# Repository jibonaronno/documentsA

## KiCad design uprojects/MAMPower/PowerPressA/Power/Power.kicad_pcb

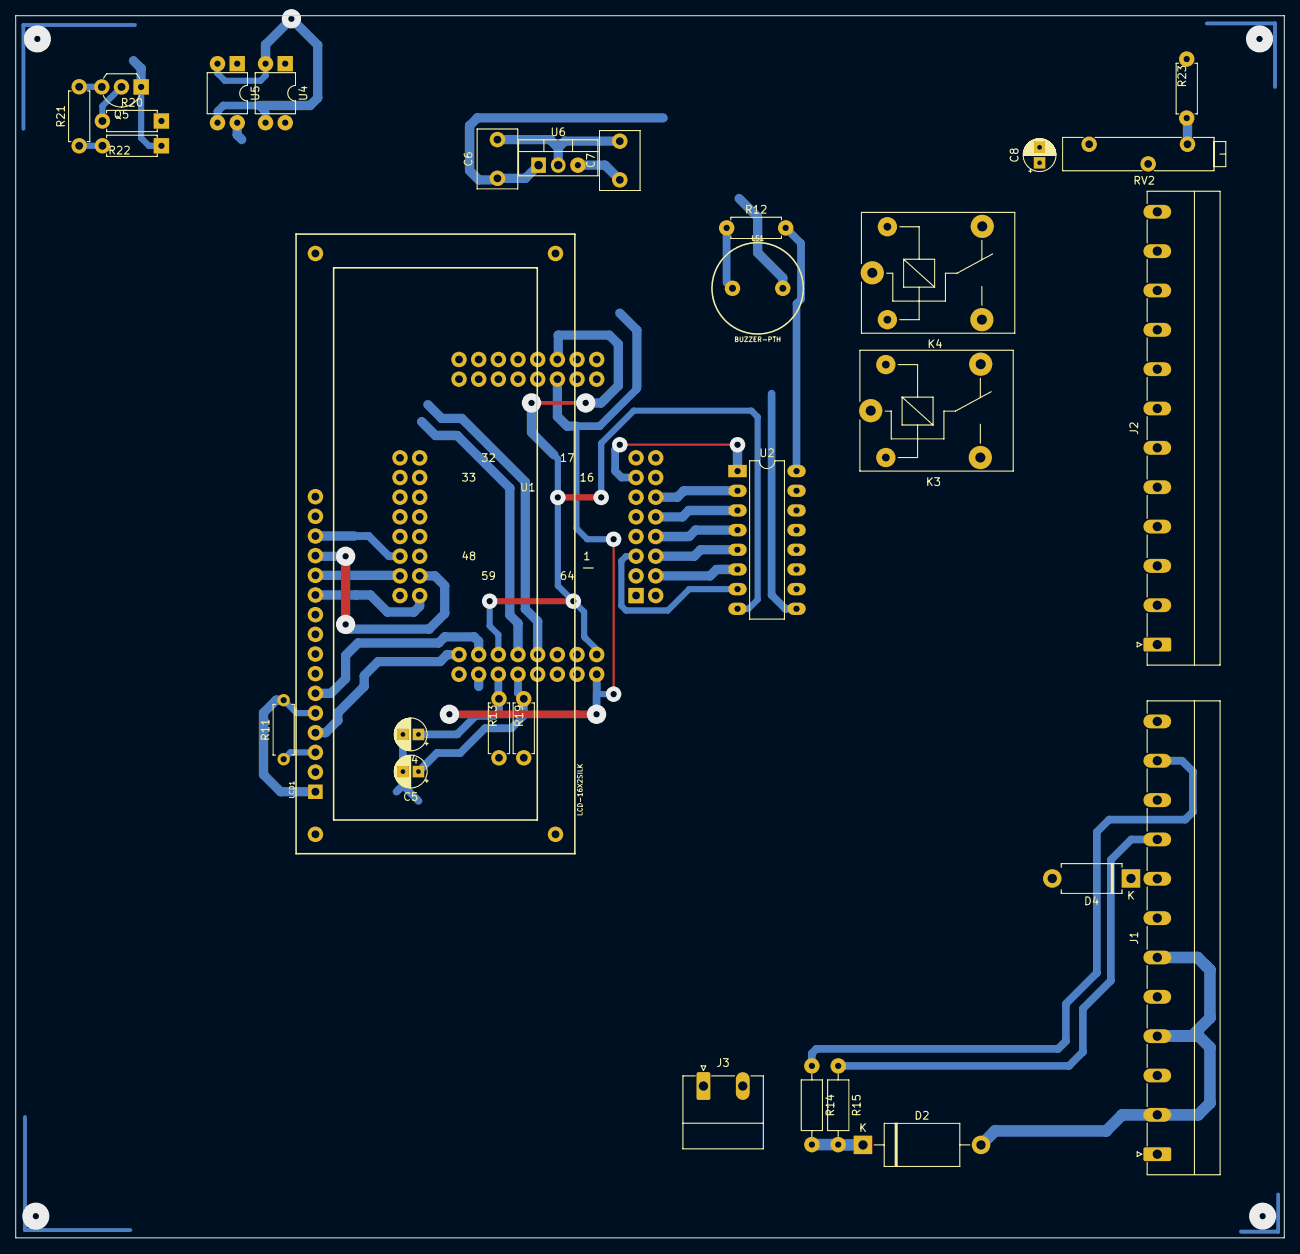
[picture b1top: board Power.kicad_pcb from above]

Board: 2 copper layers, 163.8 x 157.8 mm, 31 parts (0 on the bottom side), 39 nets.

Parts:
C4, C5, C8: CP; CP_Radial_D4.0mm_P2.00mm
C6, C7: C_Small; C_Disc_D7.5mm_W5.0mm_P5.00mm
D2: D_Small; D_DO-27_P15.24mm_Horizontal
D4: D_Small; D_DO-15_P10.16mm_Horizontal
J1, J2: Conn_01x12; PhoenixContact_MC_1,5_12-G-5.08_1x12_P5.08mm_Horizontal
J3: Conn_01x02; PhoenixContact_MC_1,5_2-G-5.08_1x02_P5.08mm_Horizontal
K3, K4: SANYOU_SRD_Form_C; Relay_SPDT_SANYOU_SRD_Series_Form_C
LCD1: LCD-16X2SILK; LCD-16X2
LS1: BUZZER-PTH; BUZZER-12MM
Q5: PN2222A; TO-92L_Inline_Wide
R11, R13, R19, R20, R22: 3K3; R_Axial_DIN0207_L6.3mm_D2.5mm_P7.62mm_Horizontal
R12: 100E; R_Axial_DIN0207_L6.3mm_D2.5mm_P7.62mm_Horizontal
R14, R15: 22K; R_Axial_DIN0207_L6.3mm_D2.5mm_P10.16mm_Horizontal
R21: 1k; R_Axial_DIN0207_L6.3mm_D2.5mm_P7.62mm_Horizontal
R23: 75K; R_Axial_DIN0207_L6.3mm_D2.5mm_P7.62mm_Horizontal
RV2: 10K; Potentiometer_Bourns_3005_Horizontal
U1: ATmega128A-AU; TQFP64.Break
U2: ULN2003A; DIP-16_W7.62mm_LongPads
U4, U5: PC817; DIP-4_W7.62mm
U6: LM7805_TO220; TO-220-3_Vertical

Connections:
10: U1.10, U2.3
12: U1.12, U2.2
13: U1.13, U2.1
48V: D2.2, J1.2, J1.4, J1.6, R23.1
+12V: C6.1, D4.2, K3.5, K4.5, LS1.+, U2.9, U6.1
+48V: D2.1, R14.2, R15.2
ADC5: C5.1, R19.1, U1.56
ADC7: C4.1, R13.1, U1.54
BKLED: R20.2, U1.40
D4: LCD1.11, U1.47
D5: LCD1.12, U1.46
D6: LCD1.13, U1.45
D7: LCD1.14, U1.44
DOOR: J1.10, U4.1
DOORT: U1.57, U4.4
E: LCD1.6, U1.51
GND: C4.2, C5.2, C6.2, C7.2, C8.2, J3.2, LCD1.1, LCD1.5, Q5.1, R11.2, R22.2, RV2.1, U1.22, U1.53, U1.63, U2.8, U4.2, U4.3, U5.2, U5.3, U6.2
LED-: LCD1.16, R21.1, R22.1
unnamed: D4.1, J1.8
unnamed: J1.1, J3.1
unnamed: J1.9, R15.1
unnamed: J1.11, R14.1
unnamed: LCD1.3, R11.1
unnamed: LS1.-, R12.1
unnamed: Q5.2, R20.1
unnamed: Q5.3, R21.2
unnamed: R12.2, U2.16
unnamed: R23.2, RV2.3
unnamed: U1.4, U2.6
unnamed: U1.5, U2.7
unnamed: U1.6, U2.5
unnamed: U1.8, U2.4
REL3: K3.2, U2.12
REL4: K4.2, U2.13
RS: LCD1.4, U1.49
VBat: C8.1, RV2.2, U1.61
VCC: C7.1, LCD1.2, LCD1.15, U1.21, U1.52, U1.64, U6.3
WATER: J1.12, U5.1
WATERT: U1.55, U5.4

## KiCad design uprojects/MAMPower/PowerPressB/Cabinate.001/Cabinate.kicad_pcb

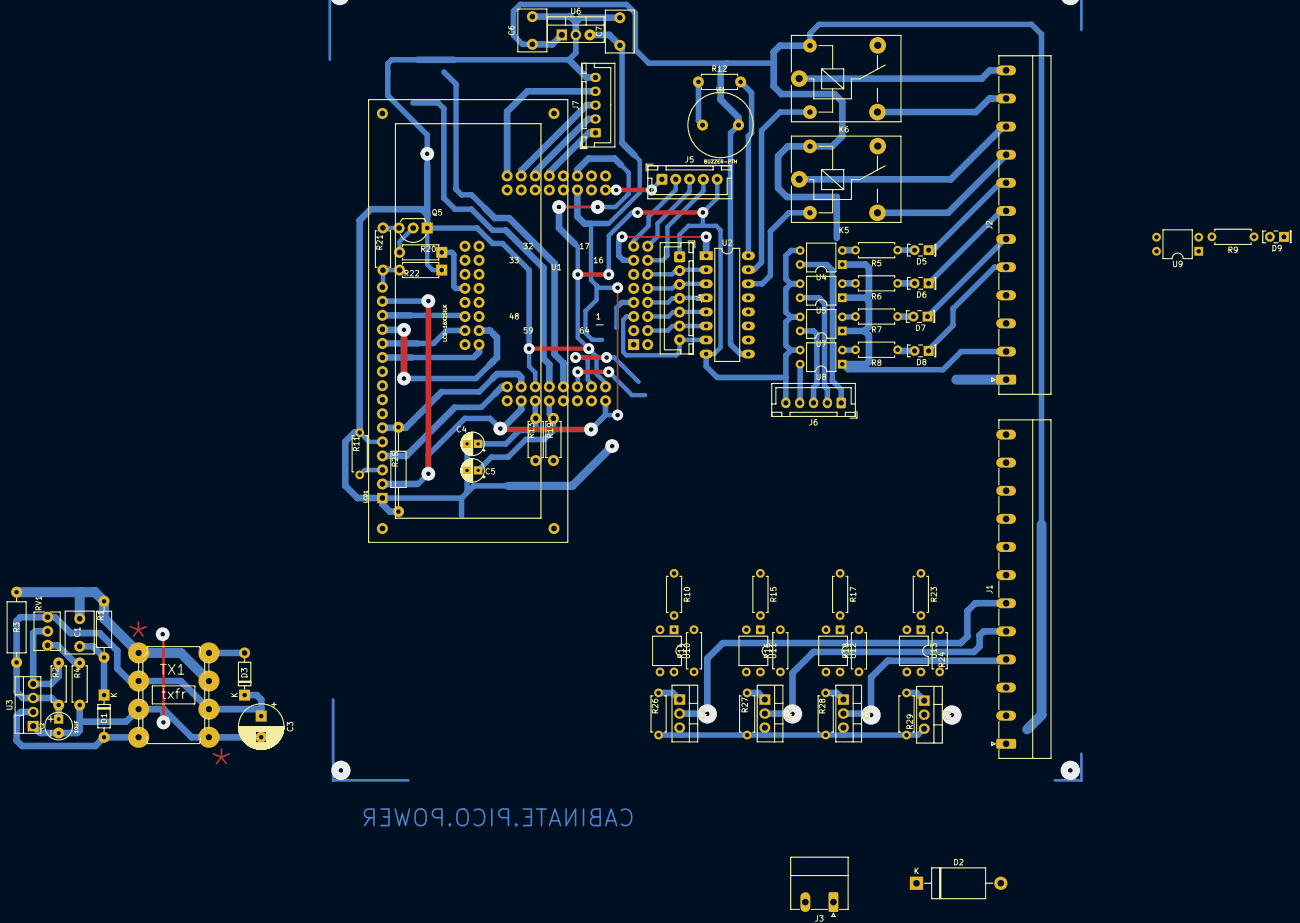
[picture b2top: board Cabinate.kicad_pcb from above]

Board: 2 copper layers, 75 parts (0 on the bottom side), 87 nets.

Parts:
C1: 103/1KV; C_Disc_D7.5mm_W5.0mm_P5.00mm
C2: 10UF; CPOL-RADIAL-2.5MM-5MM
C3: 100uF; CP_Radial_D8.0mm_P3.80mm
C4, C5: CP; CP_Radial_D4.0mm_P2.00mm
C6, C7: C_Small; C_Disc_D7.5mm_W5.0mm_P5.00mm
D1, D3: FR107; D_DO-35_SOD27_P7.62mm_Horizontal
D2: D_Small; D_DO-27_P15.24mm_Horizontal
D5, D6, D7, D8, D9: LED_Small; LED_Rectangular_W5.0mm_H2.0mm
J1, J2: Conn_01x12; PhoenixContact_MC_1,5_12-G-5.08_1x12_P5.08mm_Horizontal
J3: Conn_01x02; PhoenixContact_MC_1,5_2-G-5.08_1x02_P5.08mm_Horizontal
J4: Conn_01x07; JST_XH_B7B-XH-A_1x07_P2.50mm_Vertical
J5, J6, J7: Conn_01x05; JST_XH_B5B-XH-A_1x05_P2.50mm_Vertical
K5, K6: SANYOU_SRD_Form_C; Relay_SPDT_SANYOU_SRD_Series_Form_C
LCD1: LCD-16X2SILK; LCD-16X2
LS1: BUZZER-PTH; BUZZER-12MM
Q1, Q2, Q3, Q4: TIP122; TO-220-3_Vertical
Q5: PN2222A; TO-92L_Inline_Wide
R1: 33K1W; R_Axial_DIN0207_L6.3mm_D2.5mm_P10.16mm_Horizontal
R2: 1M; R_Axial_DIN0207_L6.3mm_D2.5mm_P7.62mm_Horizontal
R3: 47K1W; R_Axial_DIN0309_L9.0mm_D3.2mm_P12.70mm_Horizontal
R4: 2K2; R_Axial_DIN0207_L6.3mm_D2.5mm_P7.62mm_Horizontal
R5, R6, R7, R8, R9, R11, R13, R19, R20, R22: 3K3; R_Axial_DIN0207_L6.3mm_D2.5mm_P7.62mm_Horizontal
R10, R14, R15, R16, R17, R18, R23, R24: 270E; R_Axial_DIN0207_L6.3mm_D2.5mm_P7.62mm_Horizontal
R12: 100E; R_Axial_DIN0207_L6.3mm_D2.5mm_P7.62mm_Horizontal
R21: 1k; R_Axial_DIN0207_L6.3mm_D2.5mm_P7.62mm_Horizontal
R25: 3K3; R_Axial_DIN0207_L6.3mm_D2.5mm_P15.24mm_Horizontal
R26, R27, R28, R29: 100K; R_Axial_DIN0207_L6.3mm_D2.5mm_P7.62mm_Horizontal
RV1: 10K; Potentiometer_Bourns_3266Y_Vertical
TX1: txfr; -INDUCTOR_MEDIUM
U1: ATmega128A-AU; TQFP64.Break
U2: ULN2003A; DIP-16_W7.62mm_LongPads
U3: KA5L0265RTU; TO-220-4_Vertical
U4, U5, U7, U8, U9, U10, U11, U12, U13: PC817; DIP-4_W7.62mm
U6: LM7805_TO220; TO-220-3_Vertical

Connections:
4: J4.6, U1.4, U2.6
5: J4.7, U1.5, U2.7
6: J4.5, U1.6, U2.5
8: J4.4, U1.8, U2.4
10: J4.3, U1.10, U2.3
12: J4.2, U1.12, U2.2
13: U1.13, U2.1
+12V: C2.1, C3.1, C6.1, D3.1, K5.5, K6.5, LS1.+, R2.1, R3.2, RV1.3, TX1.P$2, TX1.P$6, U2.9, U3.3, U6.1
+24V: J2.2, U4.1, U5.1, U7.1, U8.1, U9.1
+48V: C1.1, D2.1, R1.2, R3.1, TX1.P$1, TX1.P$7
A1: D5.1, J2.8
A2: D7.1, J2.6
ADC5: C5.1, R19.1, U1.56
ADC7: C4.1, R13.1, U1.54
B1: D6.1, J2.7
B2: D8.1, J2.5
BKLED: R20.2, U1.40
D4: LCD1.11, U1.47
D5: LCD1.12, U1.46
D6: LCD1.13, U1.45
D7: LCD1.14, U1.44
E: LCD1.6, R25.1, U1.51
ENC1: J5.4, U1.14
ENC2: J5.2, U1.15
ENC3: J5.3, U1.16
ENC4: J5.1, U1.17
GND: C2.2, C3.2, C4.2, C5.2, C6.2, C7.2, J2.1, J3.2, J4.1, J5.5, J6.5, J7.5, LCD1.1, LCD1.5, Q1.3, Q2.3, Q3.3, Q4.3, Q5.1, R4.1, R11.2, R22.2, R25.2, R26.2, R27.2, R28.2, R29.2, TX1.P$3, TX1.P$5, U1.22, U1.53, U1.63, U2.8, U3.1, U4.3, U5.3, U6.2, U7.3, U8.3, U9.3, U10.2, U11.2, U12.2, U13.2
LED-: LCD1.16, R21.1, R22.1
unnamed: C1.2, D1.1, R1.1
unnamed: D1.2, TX1.P$4, U3.2
unnamed: D2.2, J1.2
unnamed: D3.2, TX1.P$8
unnamed: D5.2, R5.1
unnamed: D6.2, R6.1
unnamed: D7.2, R7.1
unnamed: D8.2, R8.1
unnamed: D9.2, R9.1
unnamed: J1.1, J3.1
unnamed: J2.9, K5.3
unnamed: J2.10, K5.1
unnamed: J2.11, K6.3
unnamed: J2.12, K6.1
unnamed: J6.1, U4.4
unnamed: J6.2, U5.4
unnamed: J6.3, U7.4
unnamed: J6.4, U8.4
unnamed: J7.1, U1.26
unnamed: J7.2, U1.28
unnamed: J7.3, U1.30
unnamed: J7.4, U1.32
unnamed: LCD1.3, R11.1
unnamed: LS1.-, R12.1
unnamed: Q1.1, R29.1, U13.3
unnamed: Q2.1, R27.1, U11.3
unnamed: Q3.1, R28.1, U12.3
unnamed: Q4.1, R26.1, U10.3
unnamed: Q5.2, R20.1
unnamed: Q5.3, R21.2
unnamed: R2.2, RV1.2, U3.4
unnamed: R4.2, RV1.1
unnamed: R5.2, U4.2
unnamed: R6.2, U5.2
unnamed: R7.2, U7.2
unnamed: R8.2, U8.2
unnamed: R9.2, U9.2
unnamed: R10.2, U10.1
unnamed: R12.2, U2.16
unnamed: R14.1, U10.4
unnamed: R15.2, U11.1
unnamed: R16.1, U11.4
unnamed: R17.2, U12.1
unnamed: R18.1, U12.4
unnamed: R23.2, U13.1
unnamed: R24.1, U13.4
Q4: R23.1, U1.61
Q5: R17.1, U1.59
Q6: R15.1, U1.60
Q7: R10.1, U1.58
REL5: K5.2, U2.14
REL6: K6.2, U2.15
RS: LCD1.4, U1.49
SOL1: J1.3, Q1.2
SOL2: J1.4, Q3.2
SOL3: J1.5, Q2.2
SOL4: J1.6, Q4.2
SW1: D9.1, J2.4
VCC: C7.1, LCD1.2, LCD1.15, R14.2, R16.2, R18.2, R24.2, U1.21, U1.52, U1.64, U6.3

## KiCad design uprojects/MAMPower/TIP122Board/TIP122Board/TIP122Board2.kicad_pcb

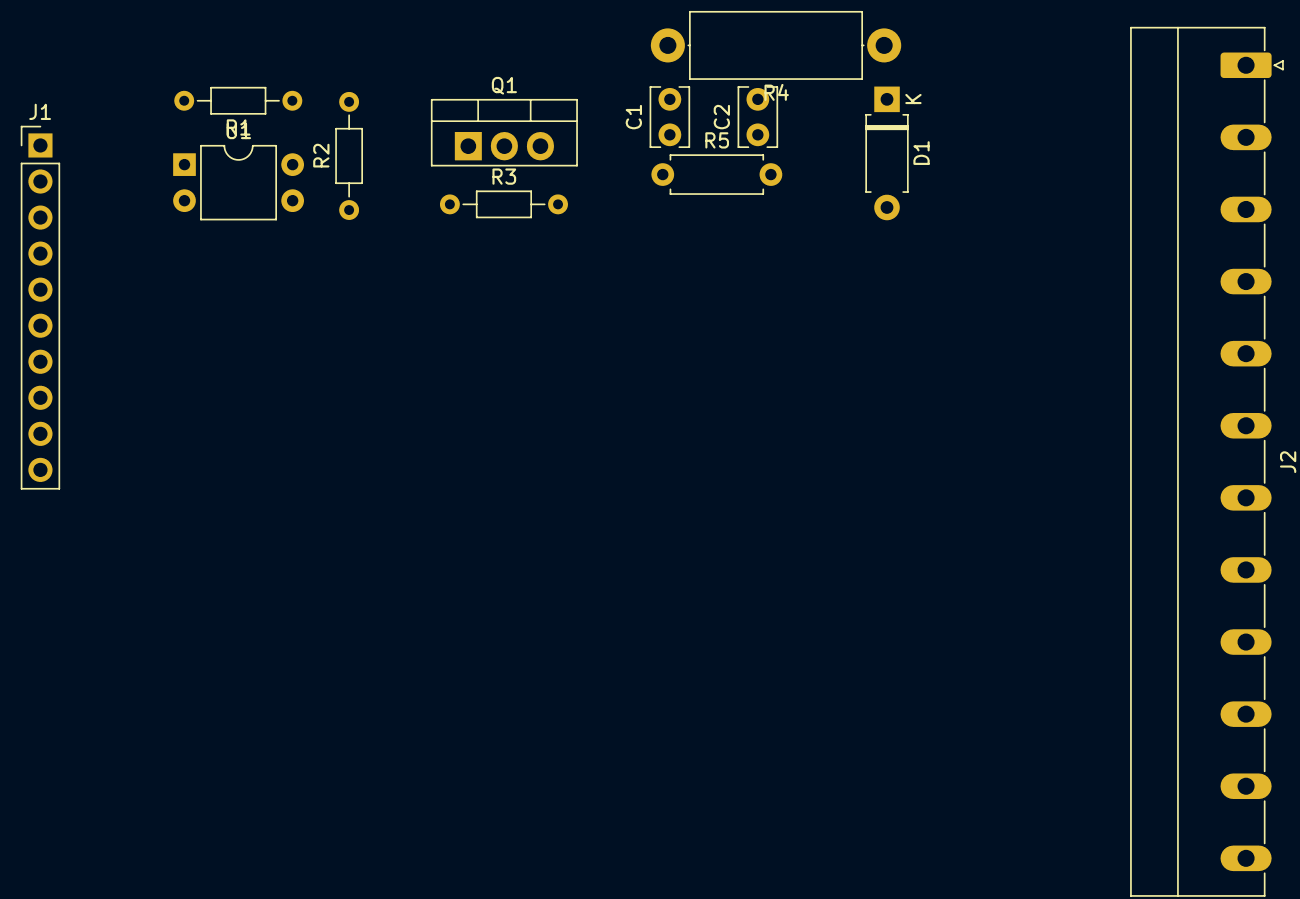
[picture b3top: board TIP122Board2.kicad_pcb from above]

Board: 2 copper layers, 12 parts (0 on the bottom side), 9 nets, no tracks yet.

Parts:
C1, C2: 0.1/400; C_Rect_L4.0mm_W2.5mm_P2.50mm
D1: D_Schottky; D_A-405_P7.62mm_Horizontal
J1: Conn_01x10; PinHeader_1x10_P2.54mm_Vertical
J2: Conn_01x12; PhoenixContact_MC_1,5_12-G-5.08_1x12_P5.08mm_Horizontal
Q1: TIP122; TO-220-3_Vertical
R1, R2: 270; R_Axial_DIN0204_L3.6mm_D1.6mm_P7.62mm_Horizontal
R3: 22K; R_Axial_DIN0204_L3.6mm_D1.6mm_P7.62mm_Horizontal
R4: 47E 5W; R_Axial_DIN0414_L11.9mm_D4.5mm_P15.24mm_Horizontal
R5: 22K 1W; R_Axial_DIN0207_L6.3mm_D2.5mm_P7.62mm_Horizontal
U1: PC817; DIP-4_W7.62mm

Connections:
24V: D1.1, J2.11
GND: J1.10, U1.2
GND2: J2.12, Q1.3, R3.2, R4.2
unnamed: C1.1, C2.1, D1.2, J2.1, Q1.2, R5.1
unnamed: C1.2, C2.2, R4.1, R5.2
unnamed: J1.1, R1.2
unnamed: Q1.1, R3.1, U1.3
unnamed: R1.1, U1.1
unnamed: R2.2, U1.4

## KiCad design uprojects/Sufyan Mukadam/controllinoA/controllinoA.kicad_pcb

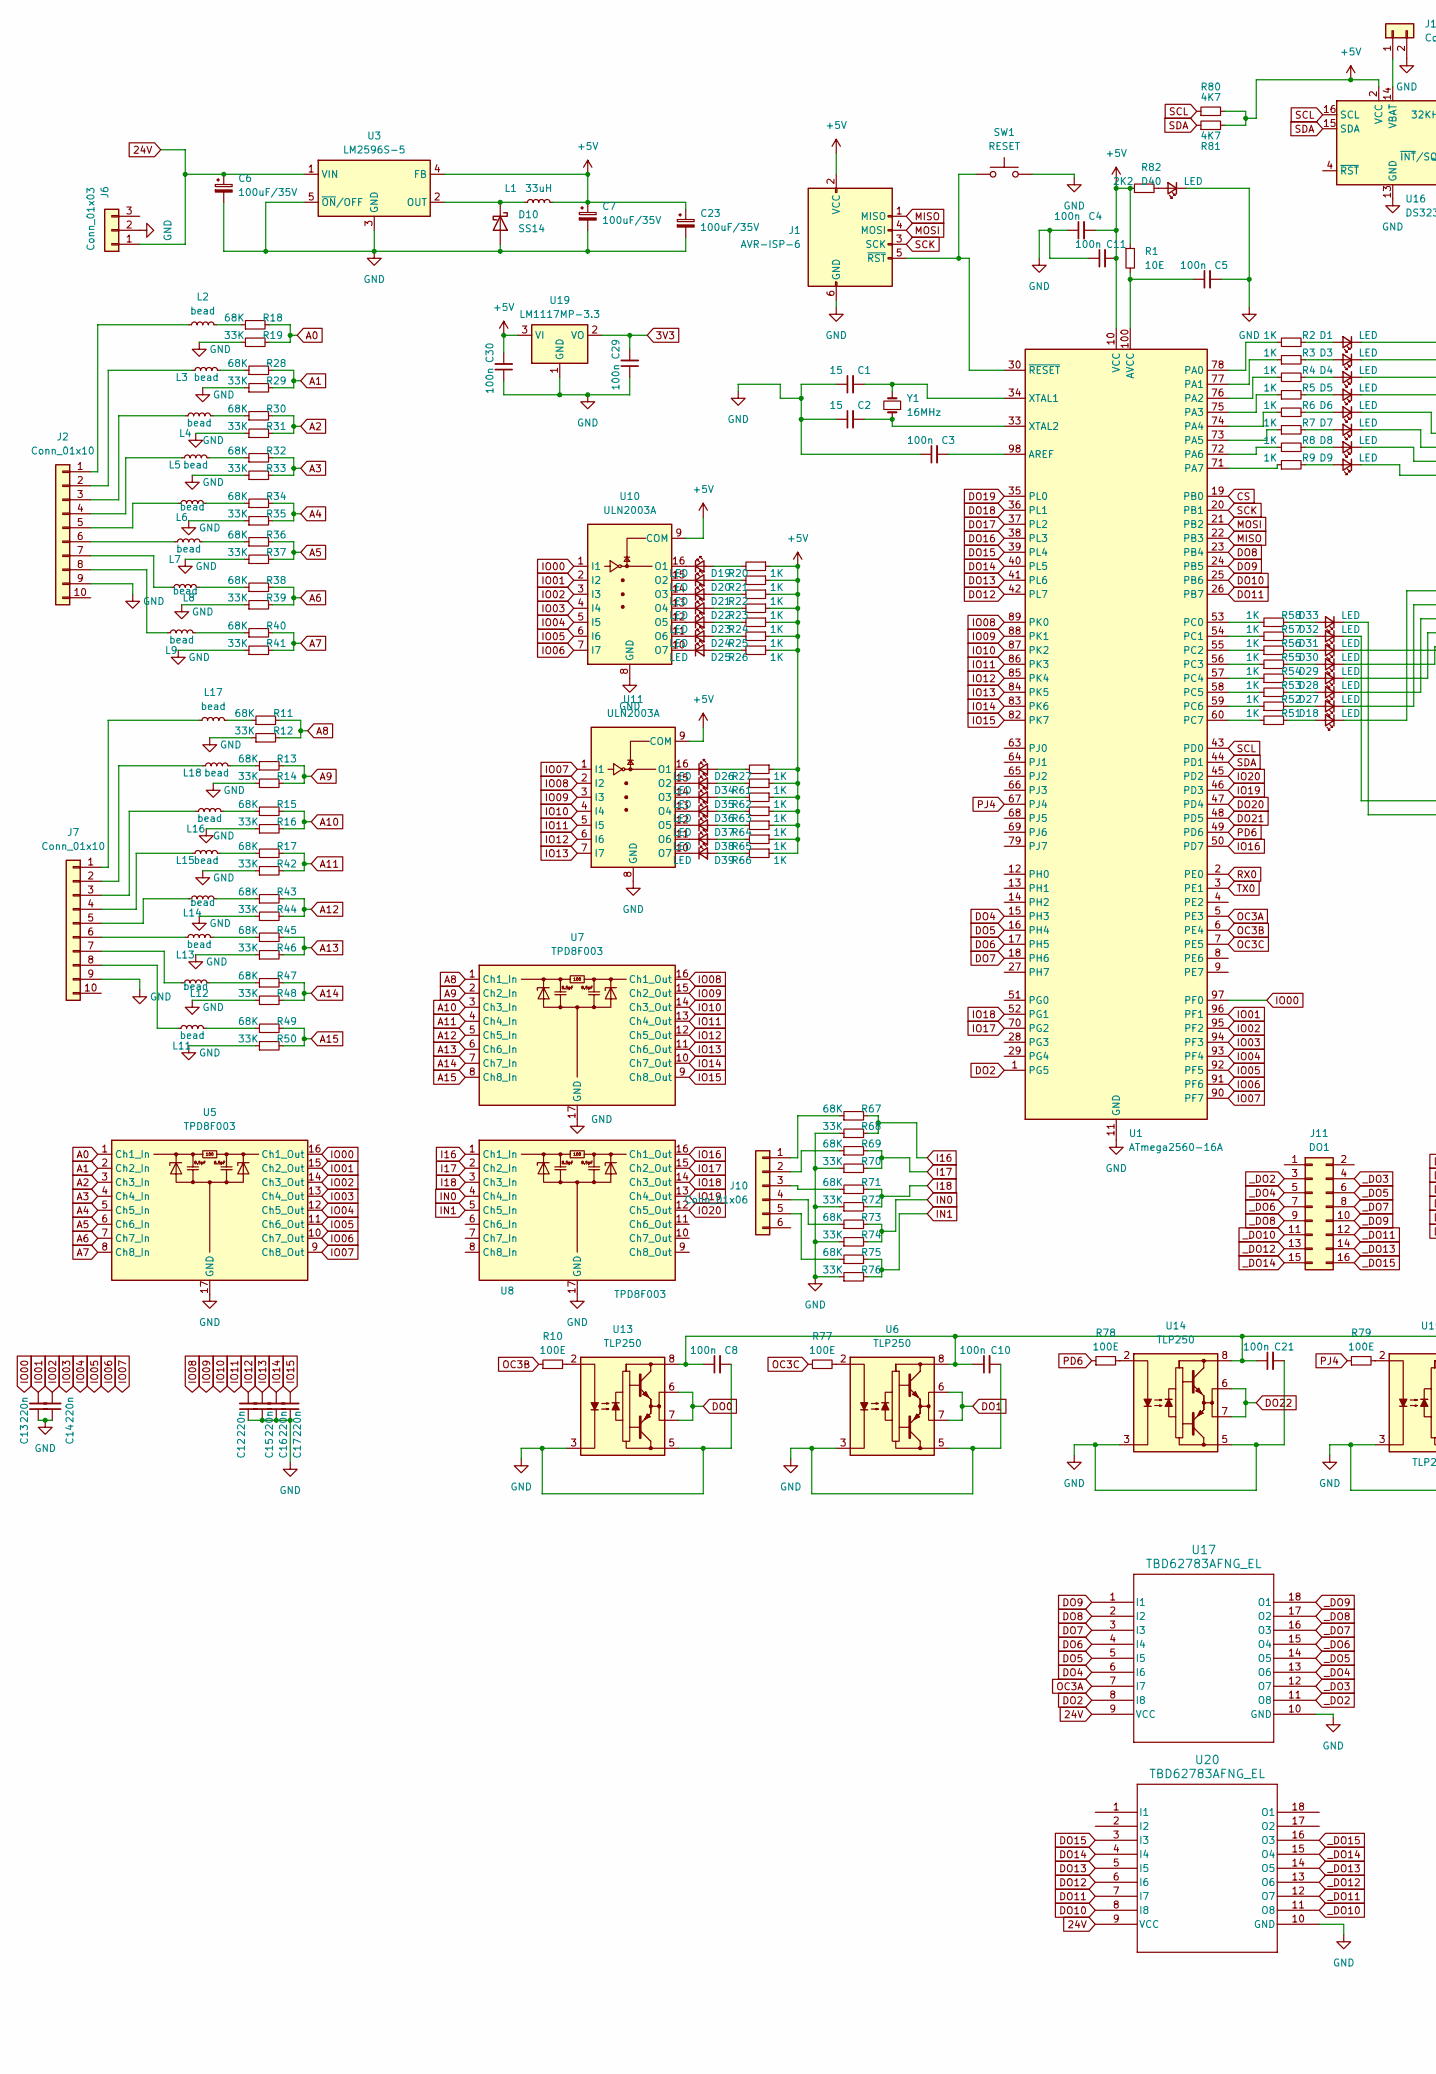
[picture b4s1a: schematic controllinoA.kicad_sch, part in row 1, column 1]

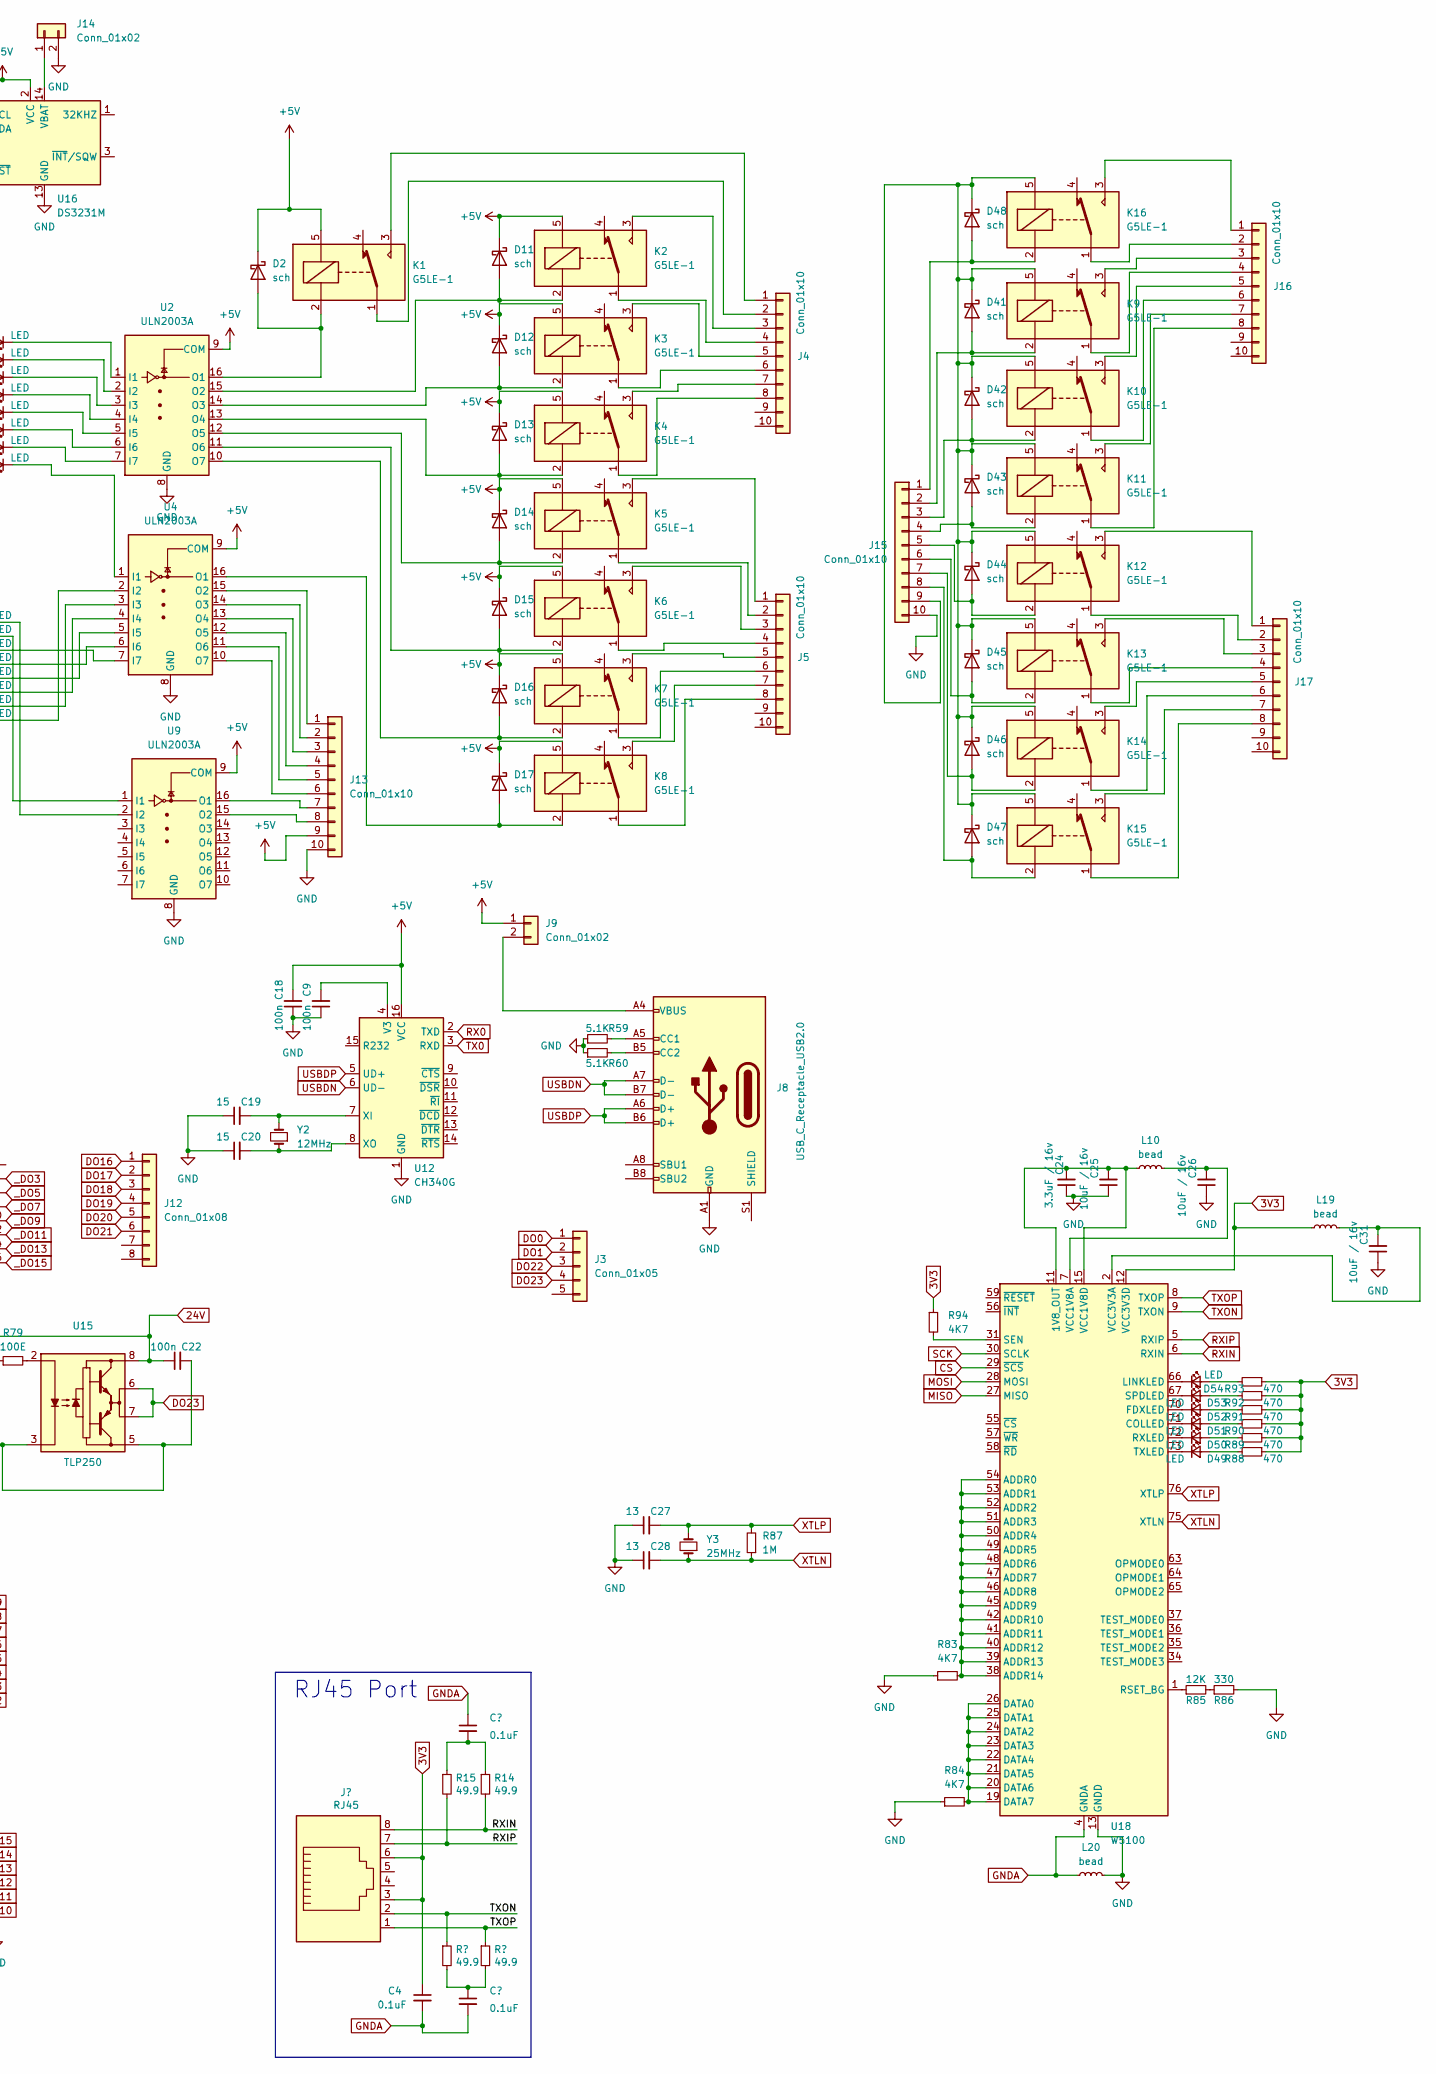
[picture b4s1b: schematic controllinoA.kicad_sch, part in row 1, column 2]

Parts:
C1, C2, C19, C20: 15; C_0805_2012Metric_Pad1.18x1.45mm_HandSolder
C3, C5, C8, C9, C10, C11, C18, C21, C22, C29, C30: 100n; C_0805_2012Metric_Pad1.18x1.45mm_HandSolder
C4, C33, C34: 0.1uF; C_0603_1608Metric
C6, C7, C23: 100uF/35V; CP_Elec_6.3x7.7
C12, C13, C14, C15, C16, C17: 220n; C_0603_1608Metric
C24: 3.3uF / 16v; C_0805_2012Metric_Pad1.18x1.45mm_HandSolder
C25, C26, C31: 10uF / 16v; C_0805_2012Metric_Pad1.18x1.45mm_HandSolder
C27, C28: 13; C_0805_2012Metric_Pad1.18x1.45mm_HandSolder
D1, D3, D4, D5, D6, D7, D8, D9, D18, D19, D20, D21, D22, D23, D24, D25, D26, D27, D28, D29, D30, D31, D32, D33, D34, D35, D36, D37, D38, D39, D40, D49, D50, D51, D52, D53, D54: LED; LED_0805_2012Metric_Pad1.15x1.40mm_HandSolder
D2, D11, D12, D13, D14, D15, D16, D17, D41, D42, D43, D44, D45, D46, D47, D48: sch; D_SOD-128
D10: SS14; D_SOD-128
J1: AVR-ISP-6; IDC-Header_2x03_P2.54mm_Vertical
J2, J7: Conn_01x10; PinHeader_1x10_P2.54mm_Vertical
J3: Conn_01x05; PinHeader_1x05_P2.54mm_Vertical
J4, J5, J16, J17: Conn_01x10; PhoenixContact_MCV_1,5_10-G-3.5_1x10_P3.50mm_Vertical
J6: Conn_01x03; PhoenixContact_MCV_1,5_3-G-5.08_1x03_P5.08mm_Vertical
J8: USB_C_Receptacle_USB2.0; USB_C_Receptacle_HCTL_HC-TYPE-C-16P-01A
J9: Conn_01x02; PinHeader_1x02_P2.54mm_Vertical
J10: Conn_01x06; PinHeader_1x06_P2.54mm_Vertical
J11: DO1; PinHeader_2x08_P2.54mm_Vertical
J12: Conn_01x08; PinHeader_1x08_P2.54mm_Vertical
J13, J15: Conn_01x10; JST_XH_B10B-XH-A_1x10_P2.50mm_Vertical
J14: Conn_01x02; JST_XH_B2B-XH-A_1x02_P2.50mm_Vertical
J18: RJ45; RJ45_Amphenol_54602-x08_Horizontal
K1, K2, K3, K4, K5, K6, K7, K8, K9, K10, K11, K12, K13, K14, K15, K16: G5LE-1; Relay_SPDT_Omron-G5LE-1
L1: 33uH; L_Bourns_SRR1210A
L2, L3, L4, L5, L6, L7, L8, L9, L10, L11, L12, L13, L14, L15, L16, L17, L18, L19, L20: bead; L_1206_3216Metric
R1: 10E; R_0805_2012Metric_Pad1.20x1.40mm_HandSolder
R2, R3, R4, R5, R6, R7, R8, R9, R20, R21, R22, R23, R24, R25, R26, R27, R51, R52, R53, R54, R55, R56, R57, R58, R61, R62, R63, R64, R65, R66: 1K; R_0805_2012Metric_Pad1.20x1.40mm_HandSolder
R10, R77, R78, R79: 100E; R_0805_2012Metric_Pad1.20x1.40mm_HandSolder
R11, R13, R17, R18, R28, R30, R32, R34, R36, R38, R40, R43, R45, R47, R49, R67, R69, R71, R73, R75: 68K; R_0805_2012Metric_Pad1.20x1.40mm_HandSolder
R12, R14, R16, R19, R29, R31, R33, R35, R37, R39, R41, R42, R44, R46, R48, R50, R68, R70, R72, R74, R76: 33K; R_0805_2012Metric_Pad1.20x1.40mm_HandSolder
R15, R96, R98: 49.9; R_0603_1608Metric
R59, R60: 5.1K; R_0805_2012Metric_Pad1.20x1.40mm_HandSolder
R80, R81, R83, R84, R94: 4K7; R_0805_2012Metric_Pad1.20x1.40mm_HandSolder
R82: 2K2; R_0805_2012Metric_Pad1.20x1.40mm_HandSolder
R85: 12K; R_0805_2012Metric_Pad1.20x1.40mm_HandSolder
R86: 330; R_0805_2012Metric_Pad1.20x1.40mm_HandSolder
R87: 1M; R_0805_2012Metric_Pad1.20x1.40mm_HandSolder
R88, R89, R90, R91, R92, R93: 470; R_0805_2012Metric_Pad1.20x1.40mm_HandSolder
SW1: RESET; SW_SPST_PTS810
U1: ATmega2560-16A; TQFP-100_14x14mm_P0.5mm
U2, U4, U9, U10, U11: ULN2003A; SOIC-16_3.9x9.9mm_P1.27mm
U3: LM2596S-5; TO-263-5_TabPin3
U5, U7, U8: TPD8F003; WSON-16_3.3x1.35_P0.4mm
U6, U13, U14, U15: TLP250; DIP-8_W7.62mm
U12: CH340G; SOIC-16_3.9x9.9mm_P1.27mm
U16: DS3231M; SOIC-16W_7.5x10.3mm_P1.27mm
U17, U20: TBD62783AFNG_EL; SSOP18-P-225-0p65_TOS
U18: W5100; LQFP-80_10x10mm_P0.4mm
U19: LM1117MP-3.3; SOT-223-3_TabPin2
Y1: 16MHz; Crystal_HC49-U_Vertical
Y2: 12MHz; Crystal_HC49-U_Vertical
Y3: 25MHz; Crystal_SMD_ECS_CSM3X-2Pin_7.6x4.1mm

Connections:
24V: C6.1, C8.1, C10.1, C21.1, C22.1, J6.1, U3.1 (VIN), U6.8 (VCC), U13.8 (VCC), U14.8 (VCC), U15.8 (VCC), U17.9 (VCC), U20.9 (VCC); also elsewhere on the board
A0: R18.2, R19.2, U5.1 (Ch1_In)
A1: R28.2, R29.2, U5.2 (Ch2_In)
A2: R30.2, R31.2, U5.3 (Ch3_In)
A3: R32.2, R33.2, U5.4 (Ch4_In)
A4: R34.2, R35.2, U5.5 (Ch5_In)
A5: R36.2, R37.2, U5.6 (Ch6_In)
A6: R38.2, R39.2, U5.7 (Ch7_In)
A7: R40.2, R41.2, U5.8 (Ch8_In)
A8: R11.2, R12.2, U7.1 (Ch1_In)
A11: R17.2, R42.2, U7.4 (Ch4_In)
A12: R43.2, R44.2, U7.5 (Ch5_In)
A13: R45.2, R46.2, U7.6 (Ch6_In)
A14: R47.2, R48.2, U7.7 (Ch7_In)
A15: R49.2, R50.2, U7.8 (Ch8_In)
CS: U1.19 (PB0), U18.29 (~SCS)
DO0: J3.1, U13.6 (VO), U13.7 (VO)
DO1: J3.2, U6.6 (VO), U6.7 (VO)
DO2: U1.1 (PG5), U17.8 (I8)
DO4: U1.15 (PH3), U17.6 (I6)
DO5: U1.16 (PH4), U17.5 (I5)
DO6: U1.17 (PH5), U17.4 (I4)
DO7: U1.18 (PH6), U17.3 (I3)
DO8: U1.23 (PB4), U17.2 (I2)
DO9: U1.24 (PB5), U17.1 (I1)
DO10: U1.25 (PB6), U20.8 (I8)
DO11: U1.26 (PB7), U20.7 (I7)
DO12: U1.42 (PL7), U20.6 (I6)
DO13: U1.41 (PL6), U20.5 (I5)
DO14: U1.40 (PL5), U20.4 (I4)
DO15: U1.39 (PL4), U20.3 (I3)
DO22: J3.3, U14.6 (VO), U14.7 (VO)
DO23: J3.4, U15.6 (VO), U15.7 (VO)
I16: R67.2, R68.2, U8.1 (Ch1_In)
I17: R69.2, R70.2, U8.2 (Ch2_In)
I18: R71.2, R72.2, U8.3 (Ch3_In)
IN0: R73.2, R74.2, U8.4 (Ch4_In)
IN1: R75.2, R76.2, U8.5 (Ch5_In)
IO00: U1.97 (PF0), U5.16 (Ch1_Out), U10.1 (I1)
IO01: C13.2, U1.96 (PF1), U5.15 (Ch2_Out), U10.2 (I2)
IO02: C14.2, U1.95 (PF2), U5.14 (Ch3_Out), U10.3 (I3)
IO03: U1.94 (PF3), U5.13 (Ch4_Out), U10.4 (I4)
IO04: U1.93 (PF4), U5.12 (Ch5_Out), U10.5 (I5)
IO05: U1.92 (PF5), U5.11 (Ch6_Out), U10.6 (I6)
IO06: U1.91 (PF6), U5.10 (Ch7_Out), U10.7 (I7)
IO07: U1.90 (PF7), U5.9 (Ch8_Out), U11.1 (I1)
IO08: U1.89 (PK0), U7.16 (Ch1_Out), U11.2 (I2)
IO09: U1.88 (PK1), U7.15 (Ch2_Out), U11.3 (I3)
IO10: U1.87 (PK2), U7.14 (Ch3_Out), U11.4 (I4)
IO11: U1.86 (PK3), U7.13 (Ch4_Out), U11.5 (I5)
IO12: C12.2, U1.85 (PK4), U7.12 (Ch5_Out), U11.6 (I6)
IO13: C15.2, U1.84 (PK5), U7.11 (Ch6_Out), U11.7 (I7)
IO14: C16.2, U1.83 (PK6), U7.10 (Ch7_Out)
IO15: C17.2, U1.82 (PK7), U7.9 (Ch8_Out)
IO16: U1.50 (PD7), U8.16 (Ch1_Out)
IO17: U1.70 (PG2), U8.15 (Ch2_Out)
IO18: U1.52 (PG1), U8.14 (Ch3_Out)
IO19: U1.46 (PD3), U8.13 (Ch4_Out)
IO20: U1.45 (PD2), U8.12 (Ch5_Out)
MISO: J1.1 (MISO), U1.22 (PB3), U18.27 (MISO)
MOSI: J1.4 (MOSI), U1.21 (PB2), U18.28 (MOSI)
unnamed: C26.2, L10.2, U18.7 (VCC1V8A), U18.74 (VCC1V8A)
unnamed: C34.1, R96.2, R98.2
unnamed: D1.2 (A), R2.2
unnamed: D1.1 (K), U2.1 (I1)
unnamed: D2.2 (A), K1.2, U2.16 (O1)
unnamed: D3.2 (A), R3.2
unnamed: D3.1 (K), U2.2 (I2)
unnamed: D4.2 (A), R4.2
unnamed: D4.1 (K), U2.3 (I3)
unnamed: D5.2 (A), R5.2
unnamed: D5.1 (K), U2.4 (I4)
unnamed: D6.2 (A), R6.2
unnamed: D6.1 (K), U2.5 (I5)
unnamed: D7.2 (A), R7.2
unnamed: D7.1 (K), U2.6 (I6)
unnamed: D8.2 (A), R8.2
unnamed: D8.1 (K), U2.7 (I7)
unnamed: D9.2 (A), R9.2
unnamed: D9.1 (K), U4.1 (I1)
unnamed: D10.1 (K), L1.1, U3.2 (OUT)
unnamed: D11.2 (A), K2.2, U2.15 (O2)
unnamed: D12.2 (A), K3.2, U2.14 (O3)
unnamed: D13.2 (A), K4.2, U2.13 (O4)
unnamed: D14.2 (A), K5.2, U2.12 (O5)
unnamed: D15.2 (A), K6.2, U2.11 (O6)
unnamed: D16.2 (A), K7.2, U2.10 (O7)
unnamed: D17.2 (A), K8.2, U4.16 (O1)
unnamed: D18.2 (A), R51.2
unnamed: D18.1 (K), U4.2 (I2)
unnamed: D19.2 (A), R20.2
unnamed: D19.1 (K), U10.16 (O1)
unnamed: D20.2 (A), R21.2
unnamed: D20.1 (K), U10.15 (O2)
unnamed: D21.2 (A), R22.2
unnamed: D21.1 (K), U10.14 (O3)
unnamed: D22.2 (A), R23.2
unnamed: D22.1 (K), U10.13 (O4)
unnamed: D23.2 (A), R24.2
unnamed: D23.1 (K), U10.12 (O5)
unnamed: D24.2 (A), R25.2
unnamed: D24.1 (K), U10.11 (O6)
unnamed: D25.2 (A), R26.2
unnamed: D25.1 (K), U10.10 (O7)
unnamed: D26.2 (A), R27.2
unnamed: D26.1 (K), U11.16 (O1)
unnamed: D27.2 (A), R52.2
unnamed: D27.1 (K), U4.3 (I3)
unnamed: D28.2 (A), R53.2
unnamed: D28.1 (K), U4.4 (I4)
unnamed: D29.2 (A), R54.2
unnamed: D29.1 (K), U4.5 (I5)
unnamed: D30.2 (A), R55.2
unnamed: D30.1 (K), U4.6 (I6)
unnamed: D31.2 (A), R56.2
unnamed: D31.1 (K), U4.7 (I7)
unnamed: D32.2 (A), R57.2
unnamed: D32.1 (K), U9.1 (I1)
unnamed: D33.2 (A), R58.2
unnamed: D33.1 (K), U9.2 (I2)
unnamed: D34.2 (A), R61.2
unnamed: D34.1 (K), U11.15 (O2)
unnamed: D35.2 (A), R62.2
unnamed: D35.1 (K), U11.14 (O3)
unnamed: D36.2 (A), R63.2
unnamed: D36.1 (K), U11.13 (O4)
unnamed: D37.2 (A), R64.2
unnamed: D37.1 (K), U11.12 (O5)
unnamed: D38.2 (A), R65.2
unnamed: D38.1 (K), U11.11 (O6)
unnamed: D39.2 (A), R66.2
unnamed: D39.1 (K), U11.10 (O7)
unnamed: D40.2 (A), R82.2
unnamed: D41.2 (A), J15.2, K9.2
unnamed: D41.1 (K), D42.1 (K), D43.1 (K), D44.1 (K), D45.1 (K), D46.1 (K), D47.1 (K), D48.1 (K), J15.9, K9.5, K10.5, K11.5, K12.5, K13.5, K14.5, K15.5, K16.5
unnamed: D42.2 (A), J15.3, K10.2
unnamed: D43.2 (A), J15.4, K11.2
unnamed: D44.2 (A), J15.5, K12.2
unnamed: D45.2 (A), J15.6, K13.2
unnamed: D46.2 (A), J15.7, K14.2
unnamed: D47.2 (A), J15.8, K15.2
unnamed: D48.2 (A), J15.1, K16.2
unnamed: D49.2 (A), R88.2
unnamed: D49.1 (K), U18.73 (TXLED)
unnamed: D50.2 (A), R89.2
unnamed: D50.1 (K), U18.72 (RXLED)
unnamed: D51.2 (A), R90.2
unnamed: D51.1 (K), U18.71 (COLLED)
unnamed: D52.2 (A), R91.2
unnamed: D52.1 (K), U18.70 (FDXLED)
unnamed: D53.2 (A), R92.2
unnamed: D53.1 (K), U18.67 (SPDLED)
unnamed: D54.2 (A), R93.2
unnamed: D54.1 (K), U18.66 (LINKLED)
unnamed: J1.5 (~RST), SW1.1, U1.30 (~RESET)
unnamed: J2.1, L2.1
unnamed: J2.2, L3.1
unnamed: J2.3, L4.1
unnamed: J2.4, L5.1
unnamed: J2.5, L6.1
unnamed: J2.6, L7.1
unnamed: J2.7, L8.1
unnamed: J2.8, L9.1
unnamed: J4.1, K1.3
unnamed: J4.2, K1.1
unnamed: J4.3, K2.3
unnamed: J4.4, K2.1
unnamed: J4.5, K3.3
unnamed: J4.6, K3.1
unnamed: J4.7, K4.3
unnamed: J4.8, K4.1
unnamed: J5.1, K5.3
unnamed: J5.2, K5.1
unnamed: J5.3, K6.3
unnamed: J5.4, K6.1
unnamed: J5.5, K7.3
unnamed: J5.6, K7.1
unnamed: J5.7, K8.3
unnamed: J5.8, K8.1
unnamed: J7.1, L17.1
unnamed: J7.2, L18.1
unnamed: J7.3, L16.1
unnamed: J7.4, L15.1
unnamed: J7.5, L14.1
unnamed: J7.6, L13.1
unnamed: J7.7, L12.1
unnamed: J7.8, L11.1
unnamed: J8.A5 (CC1), R59.2
unnamed: J8.B5 (CC2), R60.2
unnamed: J8.A4 (VBUS), J8.A9 (VBUS), J8.B4 (VBUS), J8.B9 (VBUS), J9.2
unnamed: J10.1, R67.1
unnamed: J10.2, R69.1
unnamed: J10.3, R71.1
unnamed: J10.4, R73.1
unnamed: J10.5, R75.1
unnamed: J13.1, U4.15 (O2)
unnamed: J13.2, U4.14 (O3)
unnamed: J13.3, U4.13 (O4)
unnamed: J13.4, U4.12 (O5)
unnamed: J13.5, U4.11 (O6)
unnamed: J13.6, U4.10 (O7)
unnamed: J13.7, U9.16 (O1)
unnamed: J13.8, U9.15 (O2)
unnamed: J14.1, U16.14 (VBAT)
unnamed: J16.1, K16.3
unnamed: J16.2, K16.1
unnamed: J16.3, K9.3
unnamed: J16.4, K9.1
unnamed: J16.5, K10.3
unnamed: J16.6, K10.1
unnamed: J16.7, K11.3
unnamed: J16.8, K11.1
unnamed: J17.1, K12.3
unnamed: J17.2, K12.1
unnamed: J17.3, K13.3
unnamed: J17.4, K13.1
unnamed: J17.5, K14.3
unnamed: J17.6, K14.1
unnamed: J17.7, K15.3
unnamed: J17.8, K15.1
unnamed: L2.2, R18.1
unnamed: L3.2, R28.1
unnamed: L4.2, R30.1
unnamed: L5.2, R32.1
unnamed: L6.2, R34.1
unnamed: L7.2, R36.1
unnamed: L8.2, R38.1
unnamed: L9.2, R40.1
unnamed: L11.2, R49.1
unnamed: L12.2, R47.1
unnamed: L13.2, R45.1
unnamed: L14.2, R43.1
unnamed: L15.2, R17.1
unnamed: L17.2, R11.1
unnamed: L18.2, R13.1
unnamed: R85.2, R86.1
unnamed: C3.2, U1.98 (AREF)
unnamed: C5.1, R1.2, U1.100 (AVCC)
unnamed: R2.1, U1.78 (PA0)
unnamed: R3.1, U1.77 (PA1)
unnamed: R4.1, U1.76 (PA2)
unnamed: R5.1, U1.75 (PA3)
unnamed: R6.1, U1.74 (PA4)
unnamed: R7.1, U1.73 (PA5)
unnamed: R8.1, U1.72 (PA6)
unnamed: R9.1, U1.71 (PA7)
unnamed: R58.1, U1.53 (PC0)
unnamed: R57.1, U1.54 (PC1)
unnamed: R56.1, U1.55 (PC2)
unnamed: R55.1, U1.56 (PC3)
unnamed: R54.1, U1.57 (PC4)
unnamed: R53.1, U1.58 (PC5)
unnamed: R52.1, U1.59 (PC6)
unnamed: R51.1, U1.60 (PC7)
unnamed: C1.2, U1.34 (XTAL1), Y1.2
unnamed: C2.2, U1.33 (XTAL2), Y1.1
unnamed: R77.2, U6.2 (A)
unnamed: C9.2, U12.4 (V3)
unnamed: C19.2, U12.7 (XI), Y2.2
unnamed: C20.2, U12.8 (XO), Y2.1
unnamed: R10.2, U13.2 (A)
unnamed: R78.2, U14.2 (A)
unnamed: R79.2, U15.2 (A)
unnamed: C24.2, C25.2, L10.1, U18.11 (1V8_OUT), U18.15 (VCC1V8D), U18.16 (VCC1V8D), U18.33 (VCC1V8D), U18.69 (VCC1V8D)
unnamed: R83.2, U18.38 (ADDR14), U18.39 (ADDR13), U18.40 (ADDR12), U18.41 (ADDR11), U18.42 (ADDR10), U18.45 (ADDR9), U18.46 (ADDR8), U18.47 (ADDR7), U18.48 (ADDR6), U18.49 (ADDR5), U18.50 (ADDR4), U18.51 (ADDR3), U18.52 (ADDR2), U18.53 (ADDR1), U18.54 (ADDR0)
unnamed: R84.2, U18.19 (DATA7), U18.20 (DATA6), U18.21 (DATA5), U18.22 (DATA4), U18.23 (DATA3), U18.24 (DATA2), U18.25 (DATA1), U18.26 (DATA0)
unnamed: R85.1, U18.1 (RSET_BG)
unnamed: R94.2, U18.31 (SEN)
unnamed: C31.2, L19.2, U18.2 (VCC3V3A)
OC3A: U1.5 (PE3), U17.7 (I7)
OC3B: R10.1, U1.6 (PE4)
OC3C: R77.1, U1.7 (PE5)
PD6: R78.1, U1.49 (PD6)
PJ4: R79.1, U1.67 (PJ4)
RX0: U1.2 (PE0), U12.2 (TXD)
SCK: J1.3 (SCK), U1.20 (PB1), U18.30 (SCLK)
SCL: R80.1, U1.43 (PD0), U16.16 (SCL)
SDA: R81.1, U1.44 (PD1), U16.15 (SDA)
TX0: U1.3 (PE1), U12.3 (RXD)
TXON: J18.2, R96.1, U18.9 (TXON)
TXOP: J18.1, R98.1, U18.8 (TXOP)
USBDN: J8.A7 (D-), J8.B7 (D-), U12.6 (UD-)
USBDP: J8.A6 (D+), J8.B6 (D+), U12.5 (UD+)
XTLN: C28.2, R87.1, U18.75 (XTLN), Y3.1
XTLP: C27.2, R87.2, U18.76 (XTLP), Y3.2
_DO2: J11.3, U17.11 (O8)
_DO3: J11.4, U17.12 (O7)
_DO4: J11.5, U17.13 (O6)
_DO5: J11.6, U17.14 (O5)
_DO6: J11.7, U17.15 (O4)
_DO7: J11.8, U17.16 (O3)
_DO8: J11.9, U17.17 (O2)
_DO9: J11.10, U17.18 (O1)
_DO10: J11.11, U20.11 (O8)
_DO11: J11.12, U20.12 (O7)
_DO12: J11.13, U20.13 (O6)
_DO13: J11.14, U20.14 (O5)
_DO14: J11.15, U20.15 (O4)
_DO15: J11.16, U20.16 (O3)

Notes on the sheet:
RJ45 Port

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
